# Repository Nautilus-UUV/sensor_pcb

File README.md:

# sensor_pcb
## External sensors
Those sensors just go over I2C. A connector needs to be placed on the PCB. The Leak sensor will just expose the probes.

* Temperature: https://bluerobotics.com/store/sensors-cameras/sensors/celsius-sensor-r1/
* Pressure: https://bluerobotics.com/store/sensors-cameras/sensors/bar-depth-pressure-sensor/
* Leak sensor: https://bluerobotics.com/store/sensors-cameras/leak-sensor/sos-leak-sensor/

## Internal sensors
Those are also connected to the I2C bus but are on the pcb thus internal. 

* Temperature + Humidity: SHT45-AD1B Datasheet
* Pressure Sensor: BMP581 Product Page
* Tank Pressure: ADS1115  Datesheet Note: The tank pressure is an analog signal. Plase design and layout the pcb so that a optional resistor devider could be used but normaly is not used

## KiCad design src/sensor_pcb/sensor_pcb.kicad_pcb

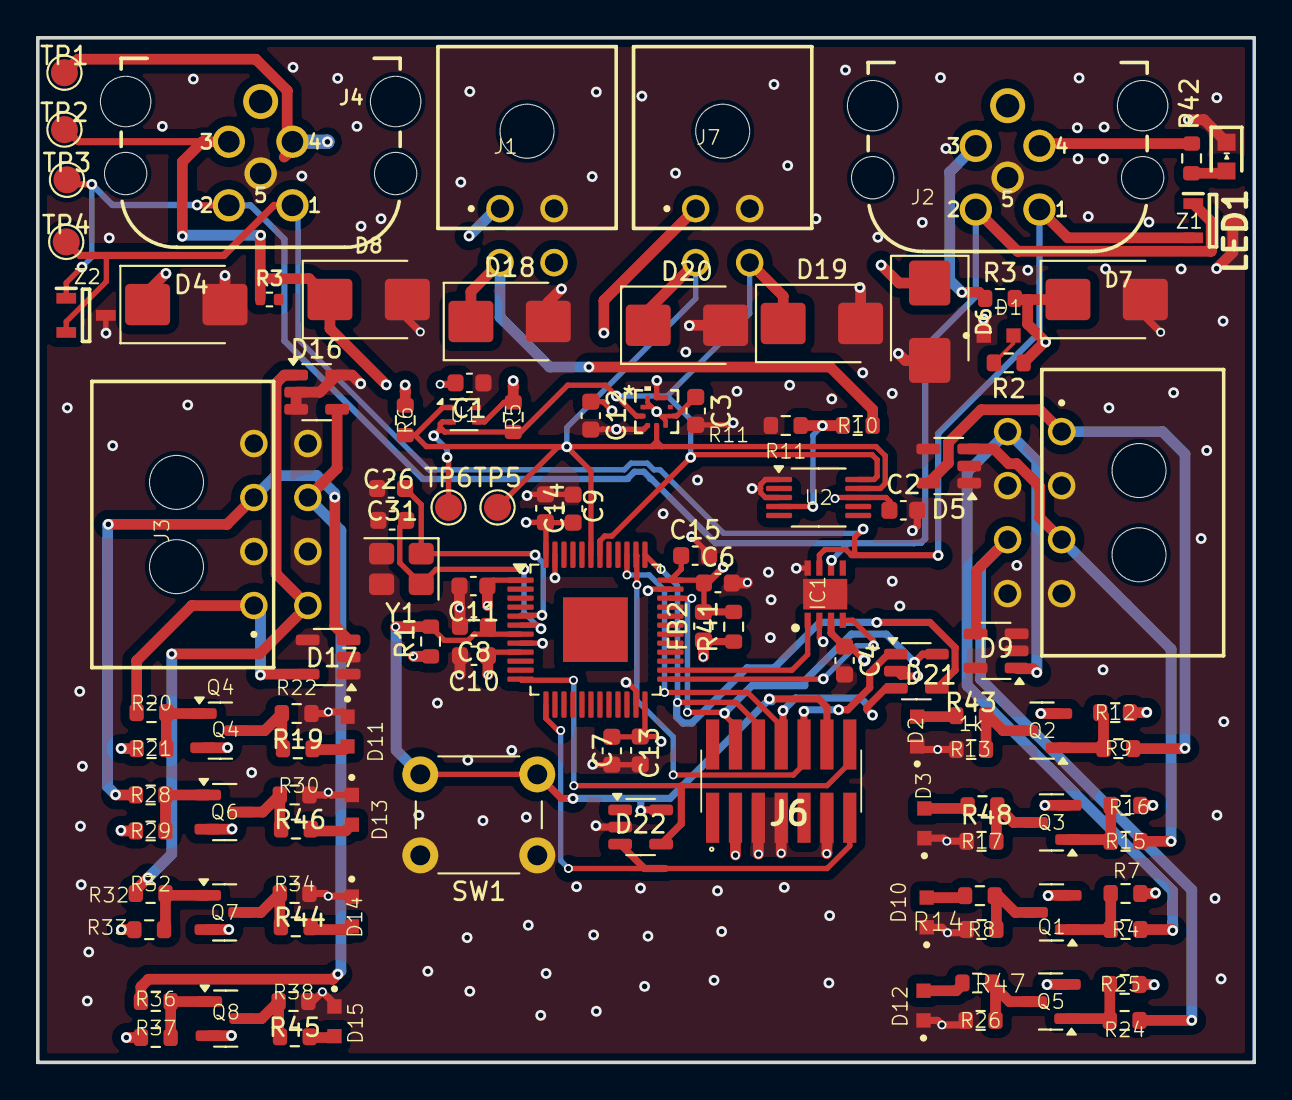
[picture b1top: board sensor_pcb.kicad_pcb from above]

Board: 4 copper layers, 67.6 x 56.9 mm, 112 parts (0 on the bottom side), 55 nets.

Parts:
C1, C2, C3, C4, C6, C8, C10, C11, C12, C13, C14: 100nF; C_0603_1608Metric
C7: 10nF; C_0603_1608Metric
C9: 1uF; C_0603_1608Metric
C15: 4.7nF; C_0603_1608Metric
C26, C31: 10pF; C_0603_1608Metric
D1: 150060RS73220; LED_0603
D2, D3, D10, D11, D12, D13, D14, D15: 150060BS73220; LED_0603
D4, D6, D7, D8, D18, D19, D20: SMBJ3.3A; D_SMB
D5, D9, D16, D17, D21, D22: 710-82402374; SOT-23-5
FB2: 100Ω@100MHz; L_0603_1608Metric
IC1: TCAN3414DRBR
J1, J7: 66200421024; Wurth_66200421024
J2, J4: 643280100305; Wuerth_WR_CIRCM_643280100305
J3, J5: 66200821024; Wurth_66200821024
J6: FTSH-107-02-L-DV; FTSH-107-XX-YYY-DV
LED1: 710-150060RS83000; Wuerth_LED_150060RS83000
Q1, Q2, Q3, Q4, Q5, Q6, Q7, Q8: NPN BJT 40V 200mA; SOT-23
R1, R5, R6: 10k; R_0603_1608Metric
R2, R3#2: 100; R_0603_1608Metric
R3: 100; R_0402_1005Metric
R4, R8, R9, R13, R14, R15, R17, R19, R20, R22, R24, R26, R28, R30, R32, R34, R36, R38, R42, R43, R44, R45, R46, R47, R48: 1k; R_0603_1608Metric
R7, R12, R16, R21, R25, R29, R33, R37: 27k; R_0603_1608Metric
R10, R11: 100k; R_0603_1608Metric
R41: 0; R_0603_1608Metric
SW1: Button Switch SPST-No; SW_PUSH_6mm
TP1, TP2, TP3, TP4, TP5, TP6: Test Point; TestPoint_Pad_D1.5mm
U1: SHT45-AD1B; Sensirion_DFN-4_1.5x1.5mm_P0.8mm_SHT4x_NoCentralPad
U2: 16-bit ADC; VSSOP-10_3x3mm_P0.5mm
U3: STM32L451CET6
U4: BMP581; QFN10_BMP581_BOS
Y1: 16.0MHz; Crystal_SMD_3225-4Pin_3.2x2.5mm
Z1, Z2: 824094024; SOT95P240X104-3N

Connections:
+3.3V: C1.2, C2.1, C3.1, C4.1, C6.1, C7.1, C9.1, C10.1, C11.1, C12.1, C13.1, C14.1, C15.1, D7.1 (K), D8.1 (K), FB2.1, FB2.2, IC1.3 (V_CC), J4.3, J6.3, J7.1, Q1.2 (E), Q2.2 (E), Q3.2 (E), Q4.2 (E), Q5.2 (E), Q6.2 (E), Q7.2 (E), Q8.2 (E), R1.1, R2.1, R3.1, R3#2.2, R5.2, R6.2, R7.1, R12.1, R16.1, R21.1, R25.1, R29.1, R33.1, R37.1, R41.1, R41.2, TP2.1, U1.3 (VDD), U2.8 (VDD), U3.1 (VBAT), U3.9 (VDDA), U3.24 (VDD), U3.36 (VDD), U3.48 (VDD), U4.1 (VDDIO), U4.5 (SDO), U4.6 (CSB), U4.10 (VDD)
+5V: D4.1 (K), D6.1 (K), J1.1, J2.4, J4.4, R42.1, TP1.1
/CAN_H: IC1.7 (CANH), J2.1, J4.1, TP4.1, Z1.2 (I/O_2), Z2.2 (I/O_2)
/CAN_L: IC1.6 (CANL), J2.2, J4.2, TP3.1, Z1.1 (I/O_1), Z2.1 (I/O_1)
/ls 1.1: D5.5 (K), J5.1, R9.1
/ls 2.1: D5.3 (K), J5.3, R15.1
/ls 3.1: D9.1 (K), J5.5, R4.1
/ls 4.1: D9.4 (K), J5.7, R24.1
/ls 5.1: D17.5 (K), J3.1, R20.1
/ls 6.1: D17.3 (K), J3.3, R28.1
/ls 7.1: D16.1 (K), J3.5, R32.1
/ls 8.1: D16.4 (K), J3.7, R36.1
/p_out: D18.1 (K), J1.3, R10.1
/s 1.1: Q2.3 (C), R13.1, R43.1
/s 2.1: Q3.3 (C), R17.1, R48.1
/s 3.1: Q1.3 (C), R8.1, R14.1
/s 4.1: Q5.3 (C), R26.1, R47.1
/s 5.1: Q4.3 (C), R19.1, R22.1
/s 6.1: Q6.3 (C), R30.1, R46.1
/s 7.1: Q7.3 (C), R34.1, R44.1
/s 8.1: Q8.3 (C), R38.1, R45.1
/sensor_stm/CAN.RX: IC1.4 (RXD), U3.25 (PB12)
/sensor_stm/CAN.TX: IC1.1 (TXD), U3.26 (PB13)
/sensor_stm/JTAG_TCK/SWCLK: D21.4 (K), J6.6, U3.37 (PA14)
/sensor_stm/JTAG_TDI: D21.1 (K), J6.10, U3.38 (PA15)
/sensor_stm/JTAG_TDO/SWD: D21.3 (K), J6.8, U3.39 (PB3)
/sensor_stm/JTAG_TMS/SWDIO: D21.5 (K), J6.4, U3.34 (PA13)
/sensor_stm/OSC_IN: C26.1, U3.5 (PH0), Y1.1
/sensor_stm/OSC_OUT: C31.1, U3.6 (PH1), Y1.4
/sensor_stm/SCL: D19.1 (K), J7.4, R5.1, TP6.1, U1.2 (SCL), U2.10 (SCL), U3.42 (PB6), U4.2 (SCK)
/sensor_stm/SDA: D20.1 (K), J7.3, R6.1, TP5.1, U1.1 (SDA), U2.9 (SDA), U3.43 (PB7), U4.4 (SDI)
/sensor_stm/UART0.RX: D22.3 (K), J6.13, U3.13 (PA3)
/sensor_stm/UART0.TX: D22.4 (K), J6.14, U3.12 (PA2)
/sensor_stm/nRST: C8.1, D22.5 (K), J6.12, R1.2, SW1.2, U3.7 (NRST)
GND: C1.1, C2.2, C3.2, C4.2, C6.2, C7.2, C8.2, C9.2, C10.2, C11.2, C12.2, C13.2, C14.2, C15.2, C26.2, C31.2, D1.C, D2.C, D3.C, D4.2 (A), D5.1 (K), D5.2 (A), D5.4 (K), D6.2 (A), D7.2 (A), D8.2 (A), D9.2 (A), D9.3 (K), D9.5 (K), D10.C, D11.C, D12.C, D13.C, D14.C, D15.C, D16.2 (A), D16.3 (K), D16.5 (K), D17.1 (K), D17.2 (A), D17.4 (K), D18.2 (A), D19.2 (A), D20.2 (A), D21.2 (A), D22.2 (A), IC1.2 (GND), IC1.8 (STB), IC1.9 (EP), J1.2, J2.5, J3.2, J3.4, J3.6, J3.8, J4.5, J5.2, J5.4, J5.6, J5.8, J6.5, J6.7, J6.11, J7.2, LED1.1 (K), R8.2, R11.2, R13.2, R17.2, R22.2, R26.2, R30.2, R34.2, R38.2, SW1.1, U1.4 (VSS), U2.1 (ADDR), U2.3 (GND), U3.8 (VSSA), U3.23 (VSS), U3.35 (VSS), U3.47 (VSS), U4.3 (VSS_1), U4.8 (VSS_2), U4.9 (VSS_3), Y1.2, Y1.3, Z1.3 (GND), Z2.3 (GND)
unnamed: D1.A, R2.2
unnamed: D2.A, R43.2
unnamed: D3.A, R48.2
unnamed: D10.A, R14.2
unnamed: D11.A, R19.2
unnamed: D12.A, R47.2
unnamed: D13.A, R46.2
unnamed: D14.A, R44.2
unnamed: D15.A, R45.2
unnamed: J2.3, R3#2.1
unnamed: LED1.2 (A), R42.2
unnamed: Q1.1 (B), R4.2, R7.2
unnamed: Q2.1 (B), R9.2, R12.2
unnamed: Q3.1 (B), R15.2, R16.2
unnamed: Q4.1 (B), R20.2, R21.2
unnamed: Q5.1 (B), R24.2, R25.2
unnamed: Q6.1 (B), R28.2, R29.2
unnamed: Q7.1 (B), R32.2, R33.2
unnamed: Q8.1 (B), R36.2, R37.2
unnamed: R10.2, R11.1, U2.4 (AIN0)

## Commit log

2025-09-23 readme add
2025-10-07 added water and temp sensor
2025-10-07 adc added
2025-10-14 pressure sensor added
2025-10-18 small fixes
2025-10-18 added connectors
2025-10-21 8 pin connectors added
2025-10-21 v1 complete
2025-11-04 schematic update
2025-11-18 intermediate changes
2025-11-18 tuesday changes
2025-11-20 fixing up parts according to kicad auto errors
2025-11-20 removed error messages
2025-12-02 finalizing pcb
2025-12-02 Sensor PCB suggestion Davide
2025-12-02 added stm
2025-12-02 pcb updates to stm
2025-12-02 clearing up errors
2025-12-03 final changes before review
2025-12-03 making schematic prettier
2025-12-09 quick changes to gnd
2025-12-09 quick save on progress
2025-12-09 bom process
2025-12-10 changes from wrong db
2025-12-10 changed to bigger footprints on resistors
2025-12-10 symbol update for spn
